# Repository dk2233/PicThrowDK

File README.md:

# PicThrowDK
Different projects for pic16f or pic18f microntrollers
It depends on PicLibDK repository 

<keep in mind that this is work in progress>

1. LED segments example - 
    
    for pic16f628a, also pic16f913 
    look to specific folders

2. DS18B20 usage with one ds18b20
    
    for pic16f913 with one or multiple sensors connected on same pin.
    
3. DS18B20 with cheap pic16f913
    System is capable of detecting id of each of the connected sensors
    and based on that communicate with them. Temperature is shown on the screen one after one sensors (second 1 is information abour normal or parasite power - 1 
    means normal)    
    Symbol shows that measurement of second connected sensor will be displayed
    
    And is displayed
    
    Symbol shows that measurement of 4th connected sensor will be displayed
    
    And is displayed

4. LED segments example in 16f84a - small, old pic16f - not very useful, but I like it very much (emotional connection)

5. LCD alphanumeric type - based on  Hitachi HD44780 or similar like KS0066. 
    
    Example of using CGRAM characters write.

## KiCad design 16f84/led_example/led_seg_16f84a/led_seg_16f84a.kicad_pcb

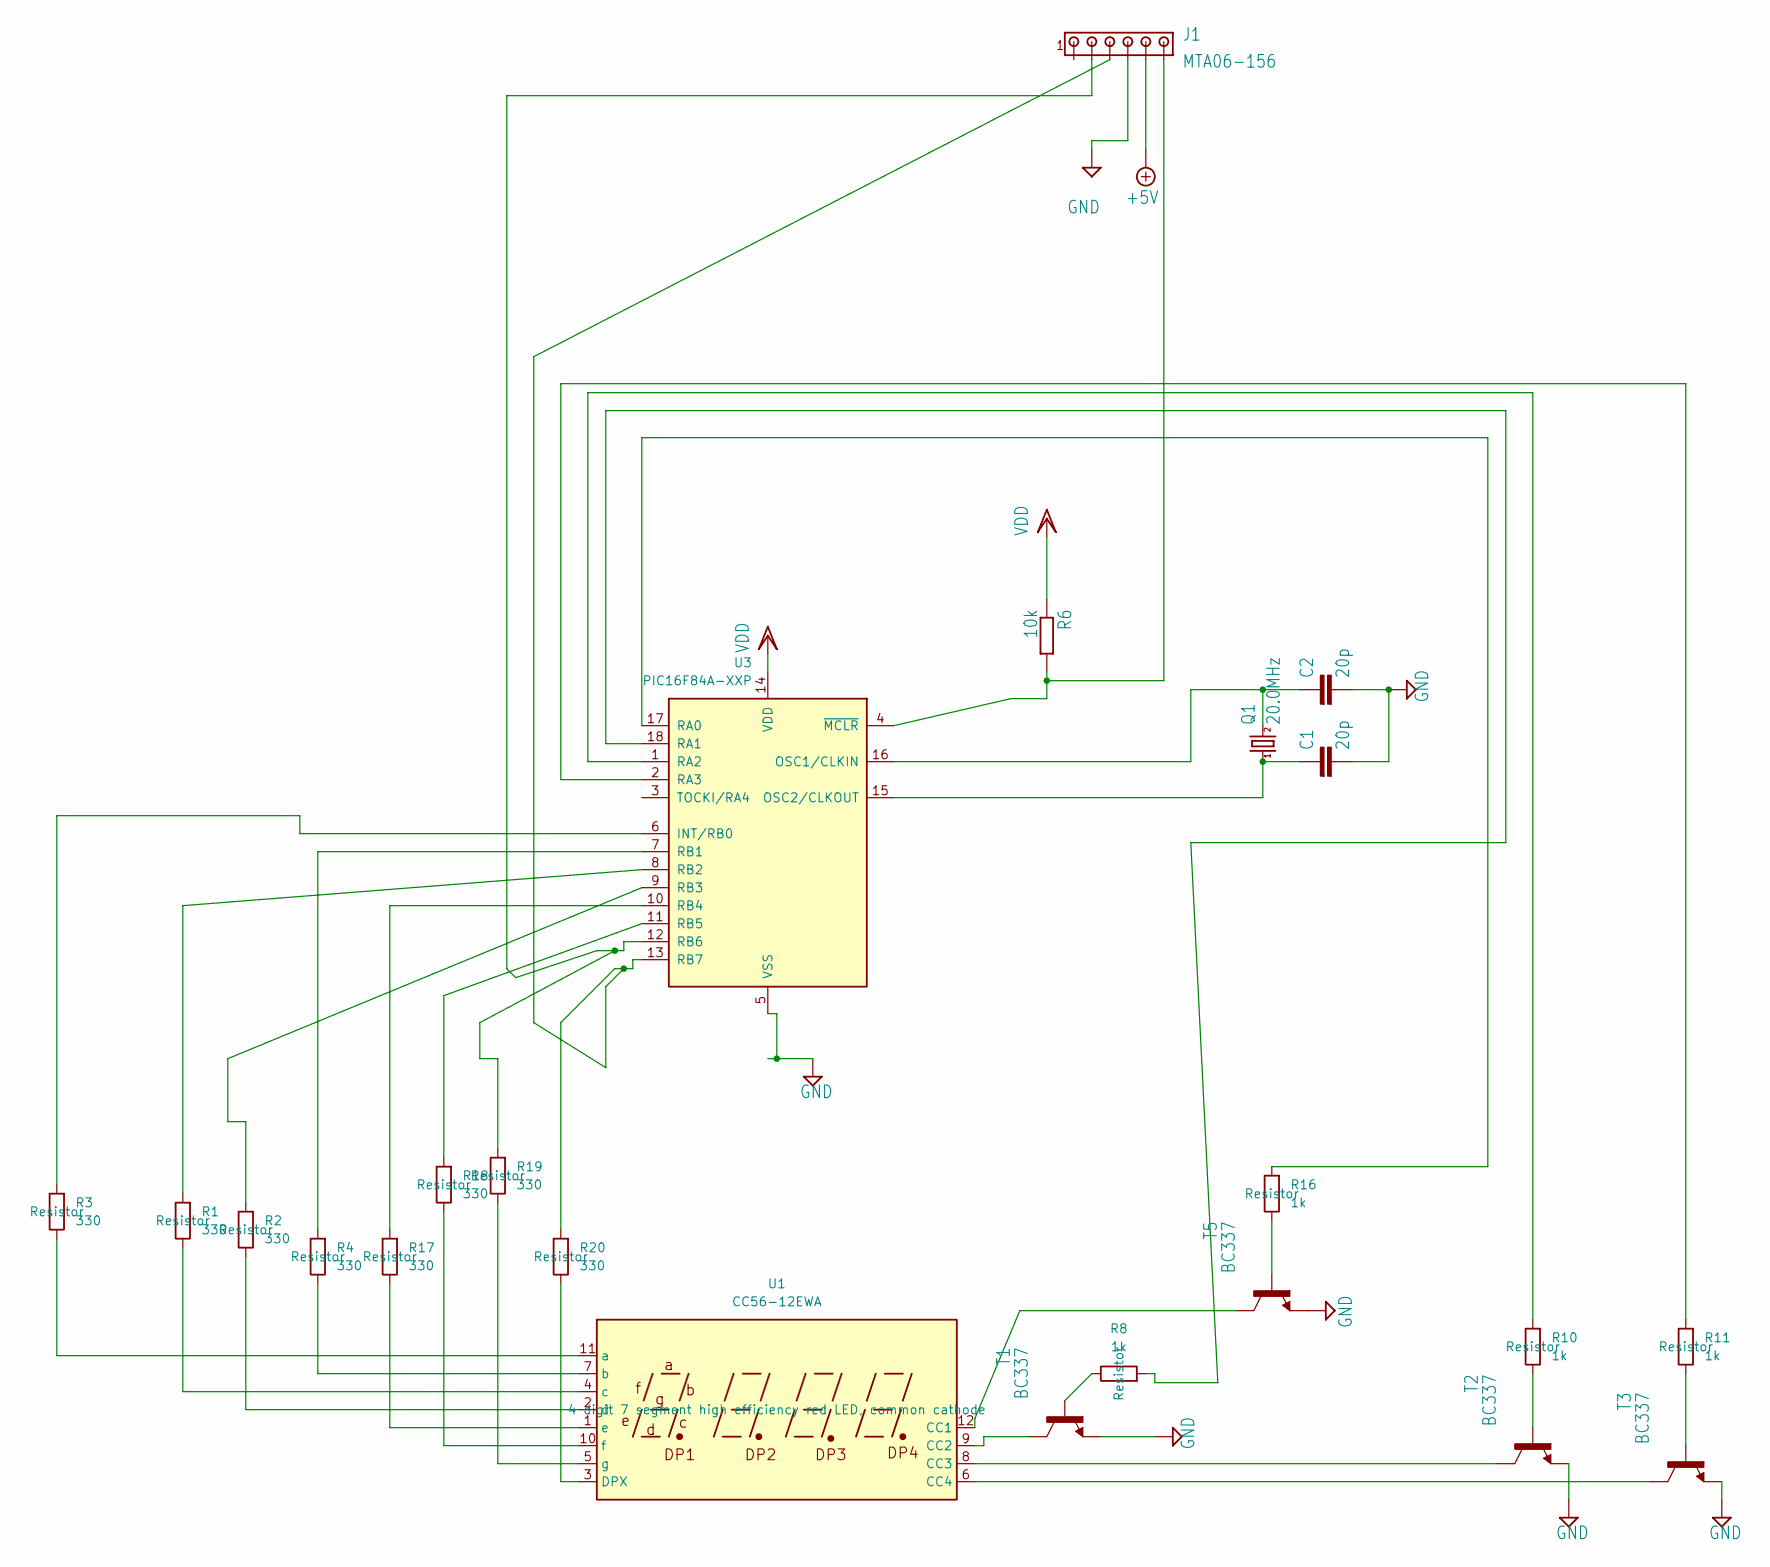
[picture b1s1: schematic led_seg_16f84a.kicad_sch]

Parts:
C1, C2: 20p; C_Disc_D4.3mm_W1.9mm_P5.00mm
J1: MTA06-156; Molex_KK-254_AE-6410-06A_1x06_P2.54mm_Vertical
Q1: 20.0MHz; Crystal_HC18-U_Vertical
R1, R2, R3, R4, R17, R18, R19, R20: 330; R_Axial_DIN0204_L3.6mm_D1.6mm_P7.62mm_Horizontal
R6: 10k; R_Axial_DIN0204_L3.6mm_D1.6mm_P7.62mm_Horizontal
R8, R10, R11, R16: 1k; R_Axial_DIN0204_L3.6mm_D1.6mm_P7.62mm_Horizontal
T1, T2, T3, T5: BC337; TO-92_Inline
U1: CC56-12EWA; CA56-12EWA
U3: PIC16F84A-XXP; DIP-18_W7.62mm

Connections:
+5V: J1.5
GND: C1.2, C2.2, J1.4, T1.1 (E), T2.1 (E), T3.1 (E), T5.1 (E), U3.5 (VSS)
unnamed: R8.1, T1.2 (B)
unnamed: T1.3 (C), U1.9 (CC2)
unnamed: R10.1, T2.2 (B)
unnamed: T2.3 (C), U1.8 (CC3)
unnamed: R11.1, T3.2 (B)
unnamed: T3.3 (C), U1.6 (CC4)
unnamed: R16.1, T5.2 (B)
unnamed: T5.3 (C), U1.12 (CC1)
unnamed: R20.1, U1.3 (DPX)
unnamed: R3.1, U1.11 (a)
unnamed: R4.1, U1.7 (b)
unnamed: R1.1, U1.4 (c)
unnamed: R2.1, U1.2 (d)
unnamed: R17.1, U1.1 (e)
unnamed: R18.1, U1.10 (f)
unnamed: R19.1, U1.5 (g)
unnamed: R3.2, U3.6 (INT/RB0)
unnamed: C2.1, Q1.2, U3.16 (OSC1/CLKIN)
unnamed: C1.1, Q1.1, U3.15 (OSC2/CLKOUT)
unnamed: R16.2, U3.17 (RA0)
unnamed: R8.2, U3.18 (RA1)
unnamed: R10.2, U3.1 (RA2)
unnamed: R11.2, U3.2 (RA3)
unnamed: R4.2, U3.7 (RB1)
unnamed: R1.2, U3.8 (RB2)
unnamed: R2.2, U3.9 (RB3)
unnamed: R17.2, U3.10 (RB4)
unnamed: R18.2, U3.11 (RB5)
unnamed: J1.2, R19.2, U3.12 (RB6)
unnamed: J1.3, R20.2, U3.13 (RB7)
unnamed: J1.6, R6.2, U3.4 (~MCLR)
VDD: R6.1, U3.14 (VDD)

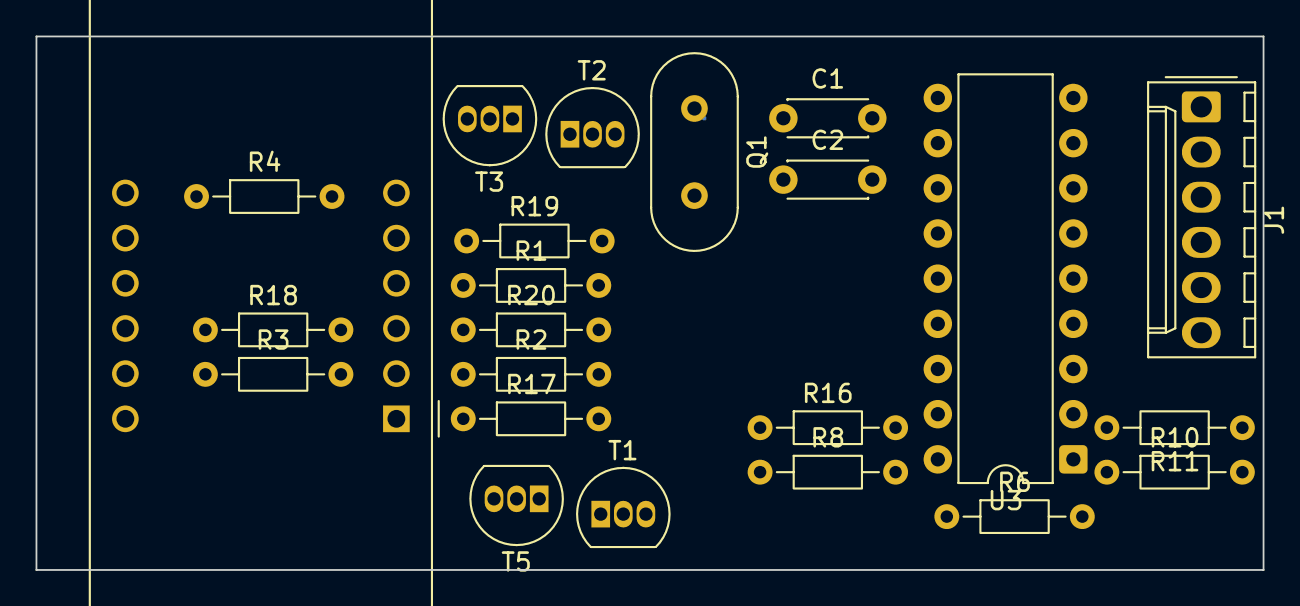
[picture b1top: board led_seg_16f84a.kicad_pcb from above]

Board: 2 copper layers, 69.0 x 30.0 mm, 23 parts (0 on the bottom side), 33 nets.

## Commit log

2025-11-10 added some projects + libs
2025-11-12 added wdg tests added more memory operations macros
2025-11-12 some cleanup
2025-11-14 led implementation also some minor updates added timer configu macros
2025-11-14 added division 24bits / 16 bits taken from piclist.com added tests http://piclist.com/techref/microchip/math/div/24by16.htm
2025-11-15 led segments 4 digits example for 16f913
2025-11-16 update of macros related to comparing 2, 3, 4 bytes
2025-11-16 added toy to blink some updates
2025-11-19 update of led procedure to be easy to use for different digits number
2025-11-20 change libs to be separate repository updated all program based on that
2025-11-20 added led digits control program on pic16f628a example how to use led_segment.inc from PicLibDK updated main README file
2025-11-21 added 16f628 dot control example updated PicLibDk commit
2025-11-24 added schematic for ds18b20 example 16f913, 16f628 move of led segment bits common control to driver
2025-11-29 ds18b20 example updated with reading power type
2025-12-01 integration of latest ds18b20 driver from PicLibDK branch added tests to verify conversion procedures added some description
2025-12-01 added procedure to store in RAM ds18b20 id
2025-12-03 added for 16f913 usage of ds18b20 search rom procedure
2025-12-05 added ds18 procedure usage to search for all connected sensors
2025-12-05 schematic update update of submodule commit
2025-12-09 added in test procedure, tests for data copying, tests for data searching in arrays,
2025-12-10 update of test to cover more tests for searching data in the array, also added Makefile and schem for test circuit
2025-12-10 test of ds18b20 updated tested for 4 sensors
2025-12-12 lcd driver handling for p16f913 (internal lcd driver)
2025-12-12 updated ds18b20 example for pic16f913 due to library changes
2025-12-14 relocatable mode test in 16f913 and usage of linker script
2025-12-15 further update of reloc mode ds18b20 test program also update integration of newer ds18 module
2025-12-18 improved reloc test project also changes related to code of PicLibDK suited to be more into reloc mode
2025-12-19 16f913 blink changed to be more like game still we can press button and led will be moved to next
2025-12-20 added blink led to be moved with key press
2025-12-22 added game choose method one game added - led move second game added test button method
2025-12-25 added tests for comparision 16 bit macro
2025-12-25 some further changes
2025-12-27 pic16f84a led digit segments usage example prepared from different modules simple every 1 sec value increment 10 MHz osc
2025-12-29 ds18b20 for pic16f84
2025-12-31 16f84a added ds18 project it uses only one sensor connected also updated ds18 absolute project for pic16f913
2026-01-02 ds18f84a integrated with driver to handle multiple ds18b20 - limitation is RAM it works fine with only 2 ds18b20 connected
2026-01-02 rename blink to led game
2026-01-03 original version of led blink reverted
2026-01-05 16f628a blink added
2026-01-08 added p16f913 blink led with random generation added blink for p16f628
2026-01-10 913 game led update
2026-01-11 key1_flags added replacing status_bits for keys added buttons2 module small update to make key detection works better
2026-01-11 changed folder name ds18b20_relocatable easier read of measurements - removed power source info
2026-01-12 update of game now it uses a internal key status not the one from macro_keys it is better due to fact - we can freely set\reset our own internal
2026-01-13 added rng in third game now works quite well
2026-01-24 lcd test 8 bit for p16f913 added tested 4 bits also for both data line in Lower and Higher nibble also tested for RW grounded (less pins used) different projects clean up
2026-02-07 update of ds18 different projects added light handle and ds18 to ds18 lcd controller project
2026-02-08 teted if ds18 driver and lcd handler can be moved to second ROM page
2026-02-13 added sdcc example with led integration of asembler macro from gpasm into c code own gplink linker
2026-02-16 added sdcc example with led integration of asembler macro from gpasm into c code interrupt usage own gplink linker
2026-02-20 added xc8 simple test project - based on sdcc test project
2026-02-20 xc8 project for lcd hd4478 tests added lcd hd4478 driver written based on lcd asembler driver
2026-02-22 further changes for xc8 lcd hitachi usage
2026-03-05 some cleanup of different folders in pic16f913 merged lcd driver into project
2026-03-20 added simple test for sdcc problem with reset and isr code
2026-04-16 xc8 hitachi lcd update of generated makefiles
